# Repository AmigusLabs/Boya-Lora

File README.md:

# Boia-Lora
### Boia con alimentación solar, para telemetria de temperatura e altuara da ola do lago de As Pontes. Datos enviados por Lora para o seu procesado.

Ano 2021 - Proxecto financiado por Xunta de Galicia

A idea do proxecto é crear unha boia que nos permita coñecer o estado do lago, ben para goce da praia ou ben para os deportes que nel practícanse.

O obxectivo era crear un  instrumento económico e efectivo para xerar os datos, e en última instancia, mellorar a comprensicón deles. Este é o principal obxectivo do proxecto, deseño, rexistro e presentación dos datos.

Os sensores a bordo da boia permítenlle medir: altura das ondas, período das ondas, potencia das ondas, temperatura da auga, temperatura do aire, presión do aire, voltaxe e consumo actual e localización GPS.

## Materiais

Para a construción completa da boia, necesita moitas cousas. Temos a desagregación dos materiais específicos requiridos en está a lista:

- Lilygo T-Beam 868mhzs
- 4 placas solares 90x60mm 6V 100mA
- INA219
- GY-86
- Sensor temperatura DS18B20
- Batería 18650
- PETG para impresión 3d
- GomaEVA
- Conectores PG7
- Regulador MT3608
- JMX-045 domo 4,5" / 114mm

## Estado:
- [ ] Desarrollo web (Rest API)
- [ ] Creación PCBs en KiCad para a electrónica
- [ ] Implementación Lora e envio a TTNv3
- [x] Implementación do software en T-BEAM de temperatua e sensores.
- [x] Implementación control enerxético
- [x] Fabricación 3d
- [x] Corte laser da Goma Eva
- [x] Deseño 2d
- [x] Deseño 3d

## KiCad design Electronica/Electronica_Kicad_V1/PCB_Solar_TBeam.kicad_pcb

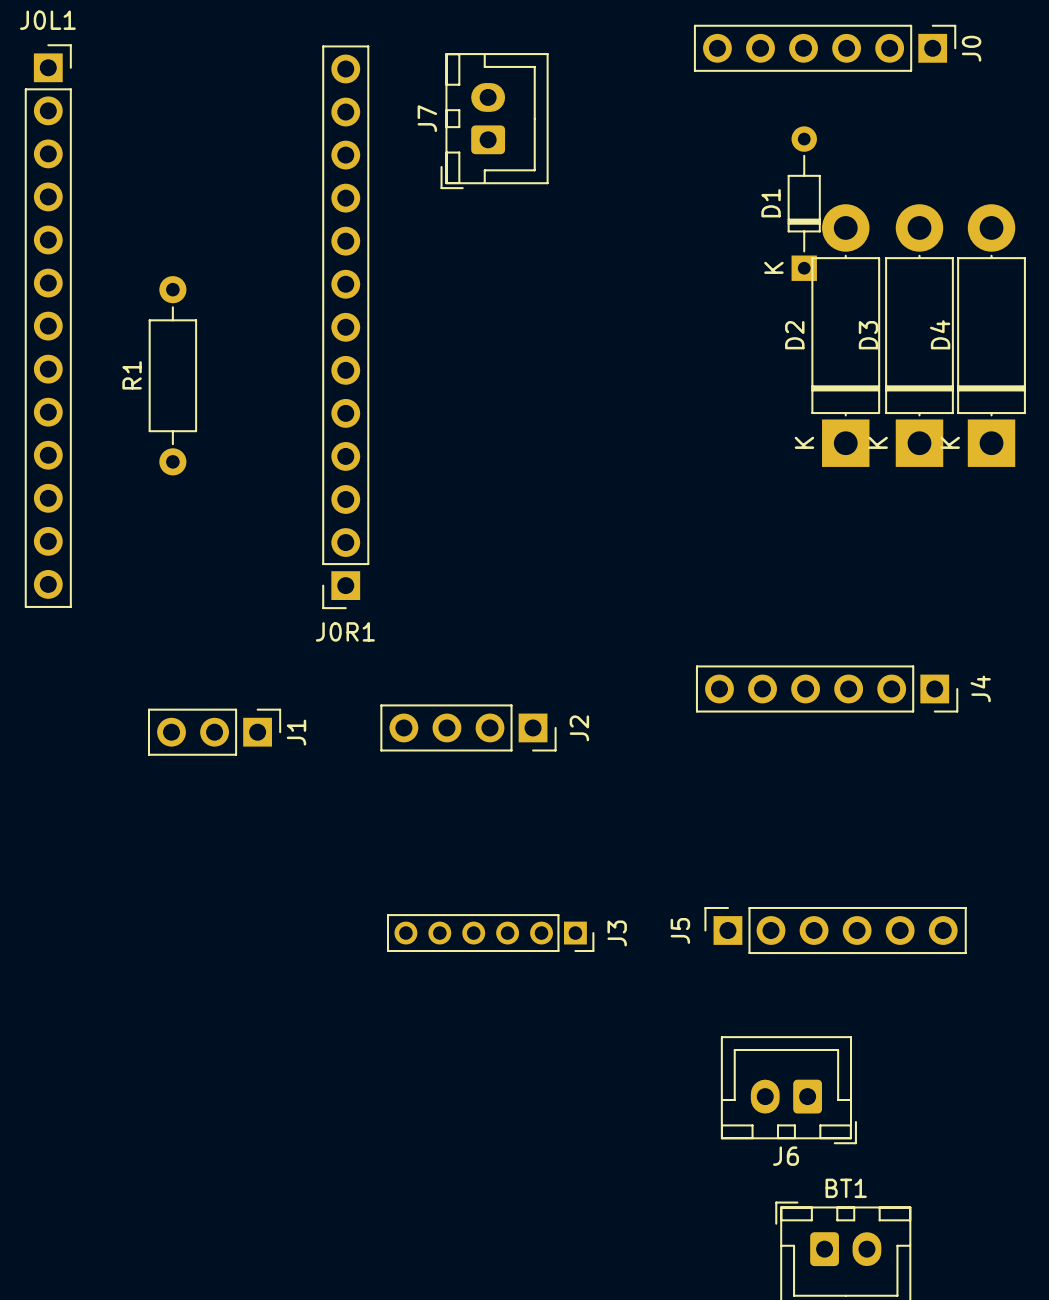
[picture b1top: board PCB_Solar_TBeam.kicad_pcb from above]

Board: 2 copper layers, 16 parts (0 on the bottom side), 15 nets, no tracks yet.

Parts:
BT1: Battery; JST_XH_B2B-XH-A_1x02_P2.50mm_Vertical
D1: D; D_DO-34_SOD68_P7.62mm_Horizontal
D2, D3, D4: D; D_5W_P12.70mm_Horizontal
J0: IN Solar Power; PinHeader_1x06_P2.54mm_Vertical
J0L1: TTGO T-beam; PinSocket_1x13_P2.54mm_Vertical
J0R1: Conn_01x13_Female; PinSocket_1x13_P2.54mm_Vertical
J1: Termometro; PinHeader_1x03_P2.54mm_Vertical
J2: GY86; PinSocket_1x04_P2.54mm_Vertical
J3: INA219; PinSocket_1x06_P2.00mm_Vertical
J4, J5: Cargador 03962A; PinSocket_1x06_P2.54mm_Vertical
J6: INA219; JST_XH_B2B-XH-A_1x02_P2.50mm_Vertical
J7: Bat IN 5V; JST_XH_B2B-XH-A_1x02_P2.50mm_Vertical
R1: 4.7K; R_Axial_DIN0207_L6.3mm_D2.5mm_P10.16mm_Horizontal

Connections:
unnamed: BT1.1, J6.1
unnamed: BT1.2, J5.5
unnamed: D1.1, D2.1, D3.1, D4.1, J4.1
unnamed: D1.2, J0.4
unnamed: D2.2, J0.3
unnamed: D3.2, J0.2
unnamed: D4.2, J0.1
unnamed: J0.6, J4.6
unnamed: J0L1.3, J1.1, J2.4, J3.6, R1.2
unnamed: J0L1.4, J2.1, J3.3
unnamed: J0L1.5, J2.2, J3.4
unnamed: J0L1.10, J1.3, R1.1
unnamed: J0R1.12, J1.2, J2.3, J3.5, J7.1
unnamed: J0R1.13, J7.2
unnamed: J5.2, J6.2

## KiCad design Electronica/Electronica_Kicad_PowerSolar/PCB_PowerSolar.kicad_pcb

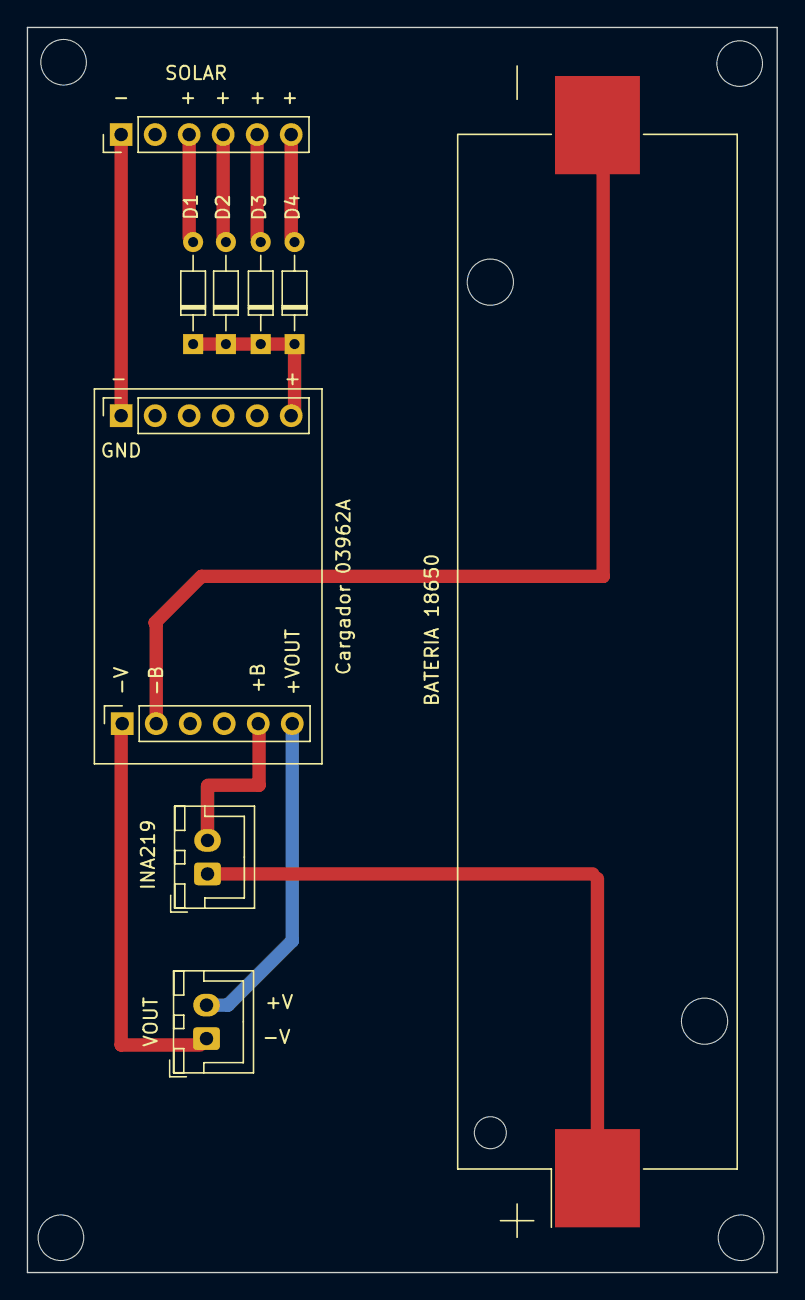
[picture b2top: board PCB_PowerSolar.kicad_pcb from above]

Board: 2 copper layers, 56.0 x 93.0 mm, 10 parts (0 on the bottom side), 11 nets.

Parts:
BATERIA 18650: Battery; BatteryHolder_Keystone_1042_1x18650
D1, D2, D3, D4: D; D_DO-34_SOD68_P7.62mm_Horizontal
INA219: INA219; JST_XH_B2B-XH-A_1x02_P2.50mm_Vertical
J1, J2: Cargador 03962A; PinSocket_1x06_P2.54mm_Vertical
SOLAR: IN Solar Power; PinHeader_1x06_P2.54mm_Vertical
VOUT: V-OUT; JST_XH_B2B-XH-A_1x02_P2.50mm_Vertical

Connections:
unnamed: BATERIA 18650.1, INA219.1
unnamed: BATERIA 18650.2, J2.2
unnamed: D1.1, D2.1, D3.1, D4.1, J1.6
unnamed: D1.2, SOLAR.3
unnamed: D2.2, SOLAR.4
unnamed: D3.2, SOLAR.5
unnamed: D4.2, SOLAR.6
unnamed: J1.1, SOLAR.1
unnamed: J2.1, VOUT.1
unnamed: INA219.2, J2.5
unnamed: J2.6, VOUT.2

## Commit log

2021-09-03 New to GitHub
    Add to GitHub
2021-09-03 NewSTL
2021-10-09 KiCad files
    En desarrollo
